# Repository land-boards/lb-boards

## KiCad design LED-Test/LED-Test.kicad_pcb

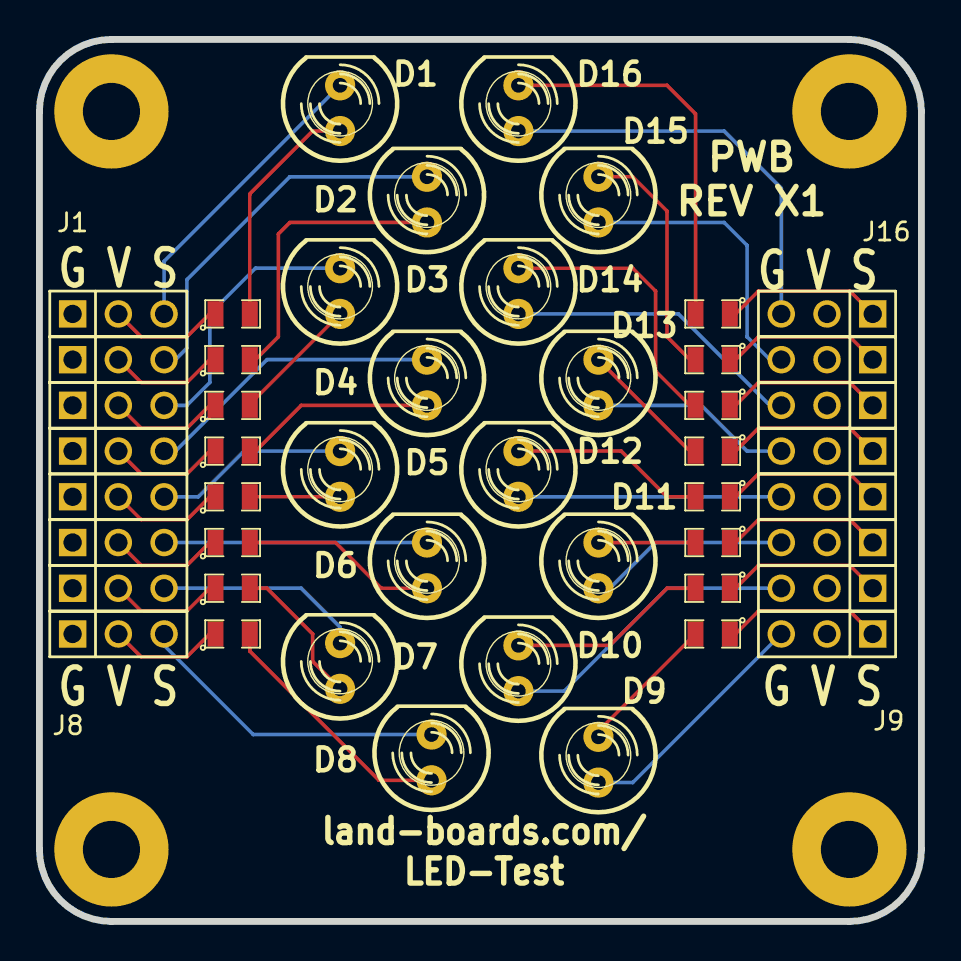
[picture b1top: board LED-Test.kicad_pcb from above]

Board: 2 copper layers, 49.0 x 49.0 mm, 52 parts (0 on the bottom side), 48 nets.

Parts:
D1, D2, D3, D4, D5, D6, D7, D8, D9, D10, D11, D12, D13, D14, D15, D16: LED; LED-5MM
J1, J2, J3, J4, J5, J6, J7, J8, J9, J10, J11, J12, J13, J14, J15, J16: CONN_3; PIN_ARRAY_3X1
MTG1, MTG2, MTG3, MTG4: CONN_1; MTG-4-40
R1, R2, R3, R4, R5, R6, R7, R8, R9, R10, R11, R12, R13, R14, R15, R16: 100; SM0805

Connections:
unnamed: J10.1, R10.1
unnamed: D10.1, J10.3
unnamed: D10.2, R10.2
unnamed: D11.2, R11.2
unnamed: J11.1, R11.1
unnamed: D11.1, J11.3
unnamed: D12.2, R12.2
unnamed: J12.1, R12.1
unnamed: J8.2, R8.1
unnamed: D8.2, J8.3
unnamed: D8.1, R8.2
unnamed: D12.1, J12.3
unnamed: D9.2, R9.2
unnamed: J9.1, R9.1
unnamed: D9.1, J9.3
unnamed: D14.2, R14.2
unnamed: D15.2, R15.2
unnamed: J15.1, R15.1
unnamed: D15.1, J15.3
unnamed: D16.2, R16.2
unnamed: J16.1, R16.1
unnamed: D16.1, J16.3
unnamed: D13.1, J13.3
unnamed: D13.2, R13.2
unnamed: J13.1, R13.1
unnamed: J14.1, R14.1
unnamed: D14.1, J14.3
unnamed: J3.2, R3.1
unnamed: D2.2, J2.3
unnamed: J2.2, R2.1
unnamed: D2.1, R2.2
unnamed: D3.1, R3.2
unnamed: D3.2, J3.3
unnamed: D4.1, R4.2
unnamed: D1.1, R1.2
unnamed: D1.2, J1.3
unnamed: J1.2, R1.1
unnamed: J6.2, R6.1
unnamed: D6.2, J6.3
unnamed: D6.1, R6.2
unnamed: D7.1, R7.2
unnamed: J7.2, R7.1
unnamed: D7.2, J7.3
unnamed: J4.2, R4.1
unnamed: D4.2, J4.3
unnamed: D5.1, R5.2
unnamed: J5.2, R5.1
unnamed: D5.2, J5.3

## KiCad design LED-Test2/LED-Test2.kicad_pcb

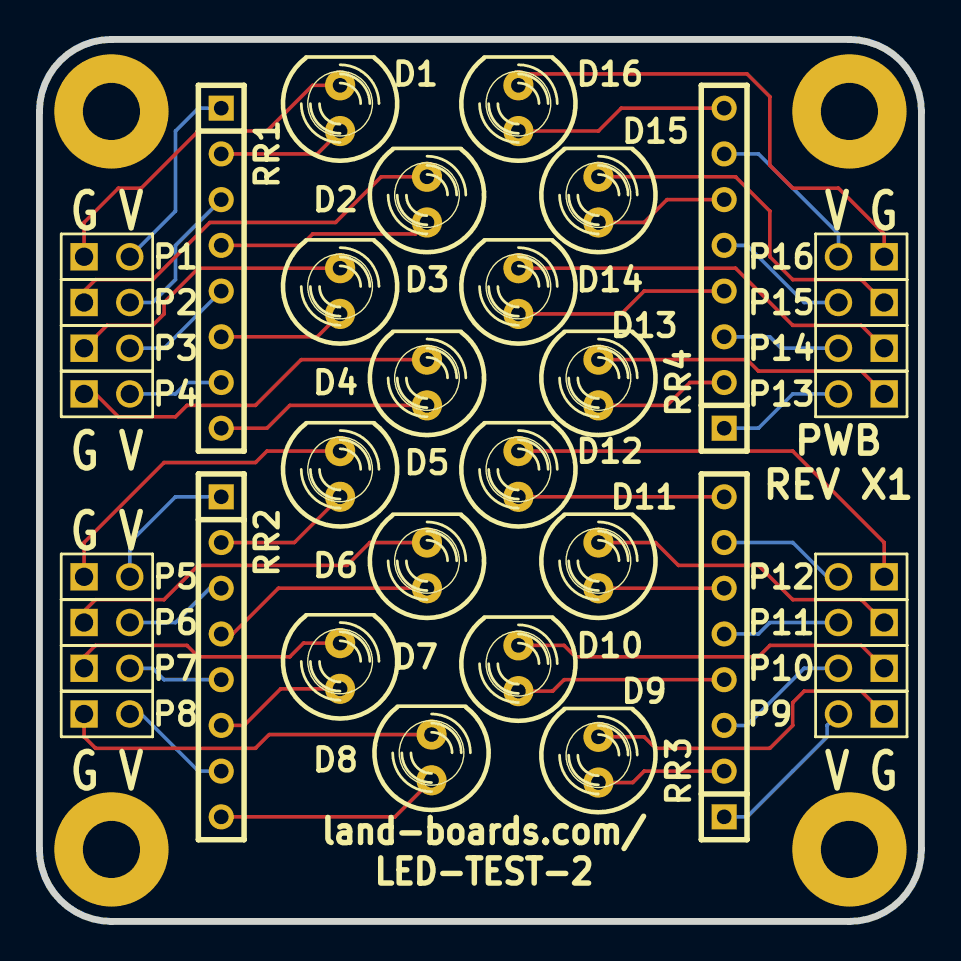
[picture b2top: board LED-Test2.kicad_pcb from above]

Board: 2 copper layers, 49.0 x 49.0 mm, 40 parts (0 on the bottom side), 48 nets.

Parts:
D1, D2, D3, D4, D5, D6, D7, D8, D9, D10, D11, D12, D13, D14, D15, D16: LED; LED-5MM
MTG1, MTG2, MTG3, MTG4: CONN_1; MTG-4-40
P1, P2, P3, P4, P5, P6, P7, P8, P9, P10, P11, P12, P13, P14, P15, P16: CONN_2; PIN_ARRAY_2X1
RR1, RR2, RR3, RR4: RR8; SIL-8

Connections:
unnamed: D5.1, RR2.2
unnamed: P6.2, RR2.3
unnamed: D6.1, RR2.4
unnamed: P7.2, RR2.5
unnamed: D7.1, RR2.6
unnamed: P8.2, RR2.7
unnamed: D8.1, RR2.8
unnamed: P10.2, RR3.3
unnamed: D10.1, RR3.4
unnamed: P11.2, RR3.5
unnamed: D11.1, RR3.6
unnamed: D2.1, RR1.4
unnamed: P3.2, RR1.5
unnamed: D3.1, RR1.6
unnamed: P4.2, RR1.7
unnamed: D4.1, RR1.8
unnamed: P9.2, RR3.1
unnamed: P5.2, RR2.1
unnamed: D14.1, RR4.4
unnamed: D15.1, RR4.6
unnamed: P13.2, RR4.1
unnamed: D13.1, RR4.2
unnamed: P14.2, RR4.3
unnamed: P15.2, RR4.5
unnamed: P16.2, RR4.7
unnamed: D16.1, RR4.8
unnamed: D9.1, RR3.2
unnamed: P12.2, RR3.7
unnamed: D12.1, RR3.8
unnamed: D6.2, P6.1
unnamed: D5.2, P5.1
unnamed: D7.2, P7.1
unnamed: D8.2, P8.1
unnamed: D9.2, P9.1
unnamed: D2.2, P2.1
unnamed: D1.1, RR1.2
unnamed: D1.2, P1.1
unnamed: P1.2, RR1.1
unnamed: D10.2, P10.1
unnamed: D3.2, P3.1
unnamed: D4.2, P4.1
unnamed: D14.2, P14.1
unnamed: D13.2, P13.1
unnamed: D15.2, P15.1
unnamed: P2.2, RR1.3
unnamed: D11.2, P11.1
unnamed: D12.2, P12.1
unnamed: D16.2, P16.1

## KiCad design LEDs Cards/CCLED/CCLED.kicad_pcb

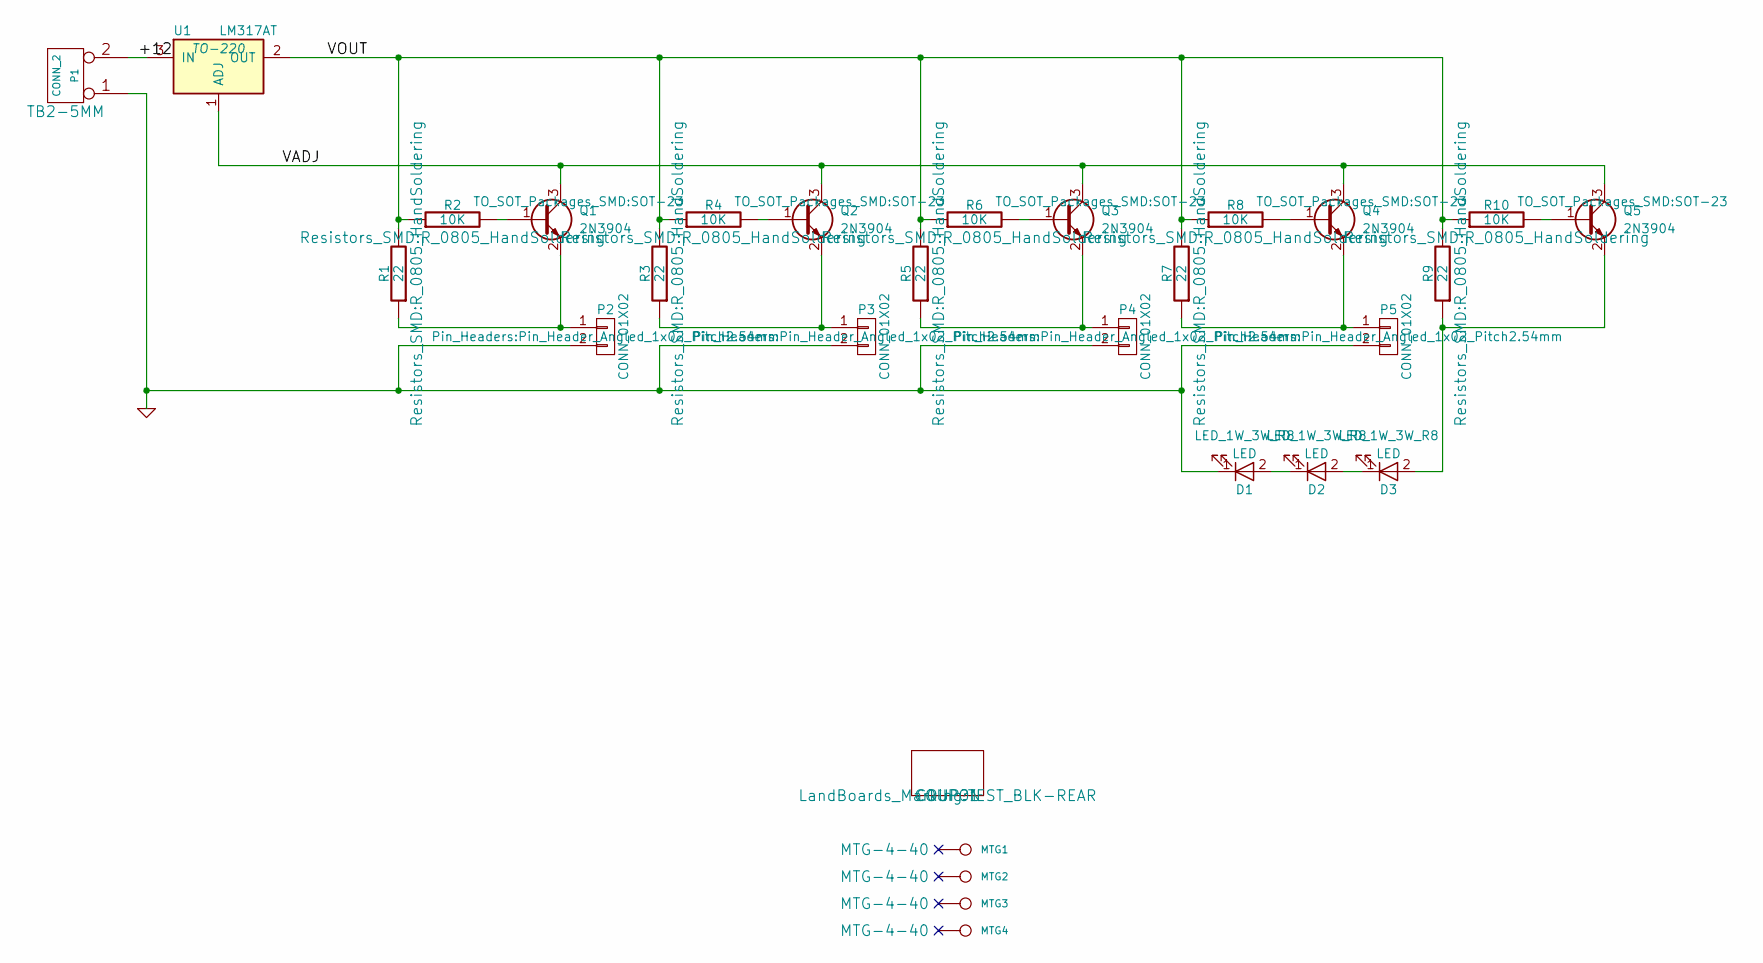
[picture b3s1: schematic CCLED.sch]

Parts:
COUP?1: COUPON; TEST_BLK-REAR
D1, D2, D3: LED; LED_1W_3W_R8
MTG1, MTG2, MTG3, MTG4: CONN_1; MTG-4-40
P1: CONN_2; TB2-5MM
P2, P3, P4, P5: CONN_01X02; Pin_Header_Angled_1x02_Pitch2.54mm
Q1, Q2, Q3, Q4, Q5: 2N3904; SOT-23
R1, R3, R5, R7, R9: 22; R_0805_HandSoldering
R2, R4, R6, R8, R10: 10K; R_0805_HandSoldering
U1: LM317AT; TO-220

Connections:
/+12: P1.2 (PM), U1.3 (IN)
/VADJ: Q1.3 (C), Q2.3 (C), Q3.3 (C), Q4.3 (C), Q5.3 (C), U1.1 (ADJ)
/VOUT: R1.2, R2.1, R3.2, R4.1, R5.2, R6.1, R7.2, R8.1, R9.2, R10.1, U1.2 (OUT)
GND: D1.1 (K), P1.1, P2.2, P3.2, P4.2, P5.2
unnamed: D1.2 (A), D2.1 (K)
unnamed: D2.2 (A), D3.1 (K)
unnamed: D3.2 (A), Q5.2 (E), R9.1
unnamed: P2.1, Q1.2 (E), R1.1
unnamed: P3.1, Q2.2 (E), R3.1
unnamed: P4.1, Q3.2 (E), R5.1
unnamed: P5.1, Q4.2 (E), R7.1
unnamed: Q1.1 (B), R2.2
unnamed: Q2.1 (B), R4.2
unnamed: Q3.1 (B), R6.2
unnamed: Q4.1 (B), R8.2
unnamed: Q5.1 (B), R10.2

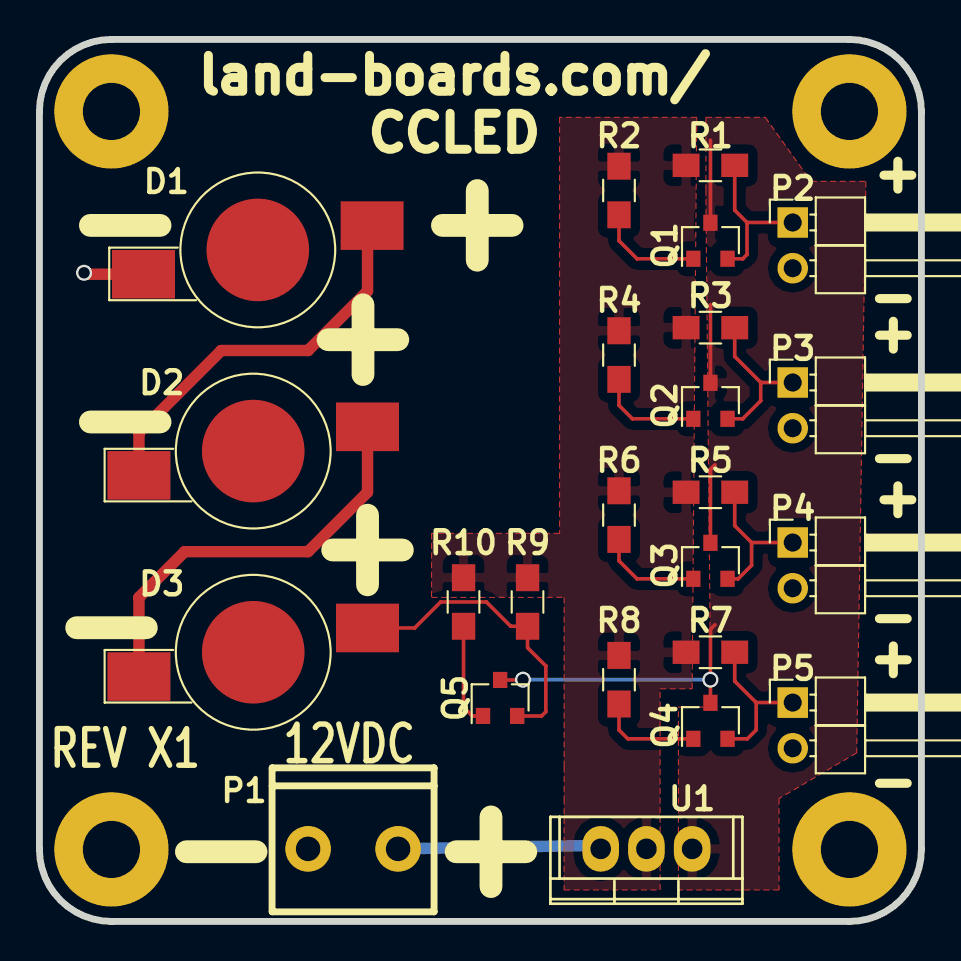
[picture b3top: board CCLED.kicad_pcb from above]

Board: 2 copper layers, 49.0 x 49.0 mm, 29 parts (0 on the bottom side), 16 nets.

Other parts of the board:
TEST: COUPON; TEST_BLK-REAR

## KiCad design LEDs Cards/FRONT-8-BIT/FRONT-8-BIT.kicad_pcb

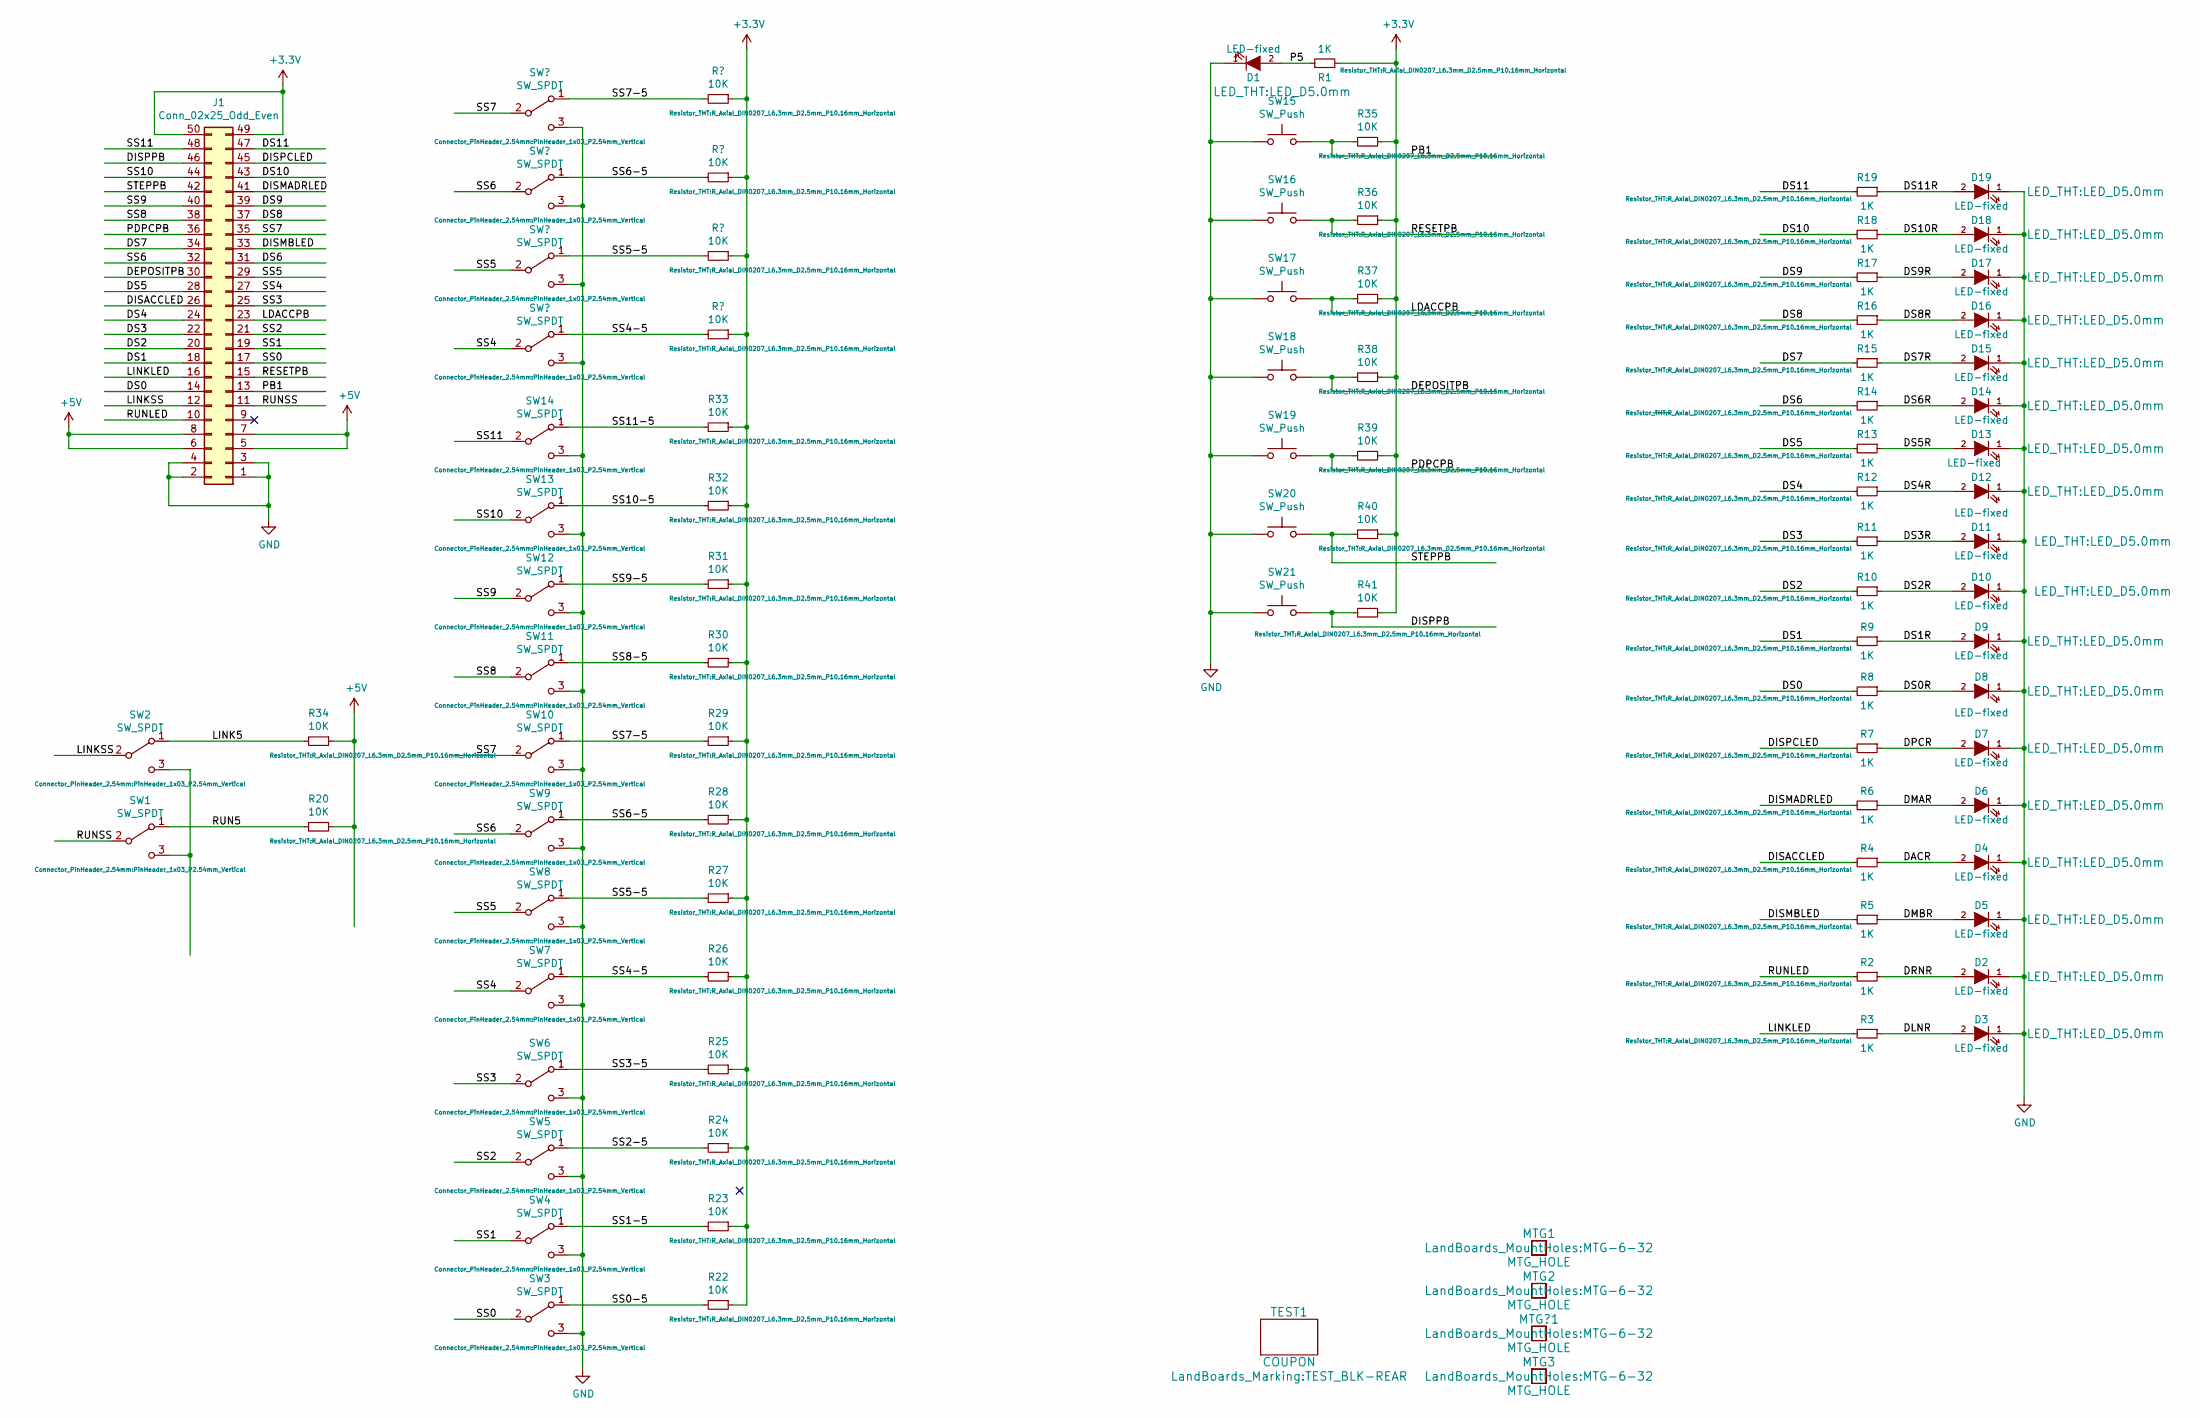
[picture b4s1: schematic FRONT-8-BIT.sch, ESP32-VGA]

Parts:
D1, D2, D3, D4, D5, D6, D7, D8, D9, D10, D11, D12, D13, D14, D15, D16, D17, D18, D19: LED-fixed; LED_D5.0mm
J1: Conn_02x25_Odd_Even; PinHeader_2x25_P2.54mm_Horizontal
MTG1, MTG2, MTG3: MTG_HOLE; MTG-6-32
MTG?1: MTG_HOLE; MTG-6-32
R1, R2, R3, R4, R5, R6, R7, R8, R9, R10, R11, R12, R13, R14, R15, R16, R17, R18, R19: 1K; R_Axial_DIN0207_L6.3mm_D2.5mm_P10.16mm_Horizontal
R20, R22, R23, R24, R25, R26, R27, R28, R29, R30, R31, R32, R33, R34, R35, R36, R37, R38, R39, R40, R41: 10K; R_Axial_DIN0207_L6.3mm_D2.5mm_P10.16mm_Horizontal
SW1, SW2, SW3, SW4, SW5, SW6, SW7, SW8, SW9, SW10, SW11, SW12, SW13, SW14: SW_SPDT; PinHeader_1x03_P2.54mm_Vertical
SW15, SW16, SW17, SW18, SW19, SW20, SW21: SW_Push; SW_PUSH_6mm_H8.5mm
TEST1: COUPON; TEST_BLK-REAR

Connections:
/DACR: D4.2 (A), R4.1
/DEPOSITPB: J1.30, R38.2, SW18.2
/DISACCLED: J1.26, R4.2
/DISMADRLED: J1.41, R6.2
/DISMBLED: J1.33, R5.2
/DISPCLED: J1.45, R7.2
/DISPPB: J1.46, R41.2, SW21.2
/DLNR: D3.2 (A), R3.1
/DMAR: D6.2 (A), R6.1
/DMBR: D5.2 (A), R5.1
/DPCR: D7.2 (A), R7.1
/DRNR: D2.2 (A), R2.1
/DS0: J1.14, R8.2
/DS0R: D8.2 (A), R8.1
/DS1: J1.18, R9.2
/DS1R: D9.2 (A), R9.1
/DS2: J1.20, R10.2
/DS2R: D10.2 (A), R10.1
/DS3: J1.22, R11.2
/DS3R: D11.2 (A), R11.1
/DS4: J1.24, R12.2
/DS4R: D12.2 (A), R12.1
/DS5: J1.28, R13.2
/DS5R: D13.2 (A), R13.1
/DS6: J1.31, R14.2
/DS6R: D14.2 (A), R14.1
/DS7: J1.34, R15.2
/DS7R: D15.2 (A), R15.1
/DS8: J1.37, R16.2
/DS8R: D16.2 (A), R16.1
/DS9: J1.39, R17.2
/DS9R: D17.2 (A), R17.1
/DS10: J1.43, R18.2
/DS10R: D18.2 (A), R18.1
/DS11: J1.47, R19.2
/DS11R: D19.2 (A), R19.1
/LDACCPB: J1.23, R37.2, SW17.2
/LINK5: R34.2, SW2.1 (A)
/LINKLED: J1.16, R3.2
/LINKSS: J1.12, SW2.2 (B)
/P5: D1.2 (A), R1.1
/PB1: J1.13, R35.2, SW15.2
/PDPCPB: J1.36, R39.2, SW19.2
/RESETPB: J1.15, R36.2, SW16.2
/RUN5: R20.2, SW1.1 (A)
/RUNLED: J1.10, R2.2
/RUNSS: J1.11, SW1.2 (B)
/SS0: J1.17, SW3.2 (B)
/SS0-5: R22.2, SW3.1 (A)
/SS1: J1.19, SW4.2 (B)
/SS1-5: R23.2, SW4.1 (A)
/SS2: J1.21, SW5.2 (B)
/SS2-5: R24.2, SW5.1 (A)
/SS3: J1.25, SW6.2 (B)
/SS3-5: R25.2, SW6.1 (A)
/SS4: J1.27, SW7.2 (B)
/SS4-5: R26.2, SW7.1 (A)
/SS5: J1.29, SW8.2 (B)
/SS5-5: R27.2, SW8.1 (A)
/SS6: J1.32, SW9.2 (B)
/SS6-5: R28.2, SW9.1 (A)
/SS7: J1.35, SW10.2 (B)
/SS7-5: R29.2, SW10.1 (A)
/SS8: J1.38, SW11.2 (B)
/SS8-5: R30.2, SW11.1 (A)
/SS9: J1.40, SW12.2 (B)
/SS9-5: R31.2, SW12.1 (A)
/SS10: J1.44, SW13.2 (B)
/SS10-5: R32.2, SW13.1 (A)
/SS11: J1.48, SW14.2 (B)
/SS11-5: R33.2, SW14.1 (A)
/STEPPB: J1.42, R40.2, SW20.2

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
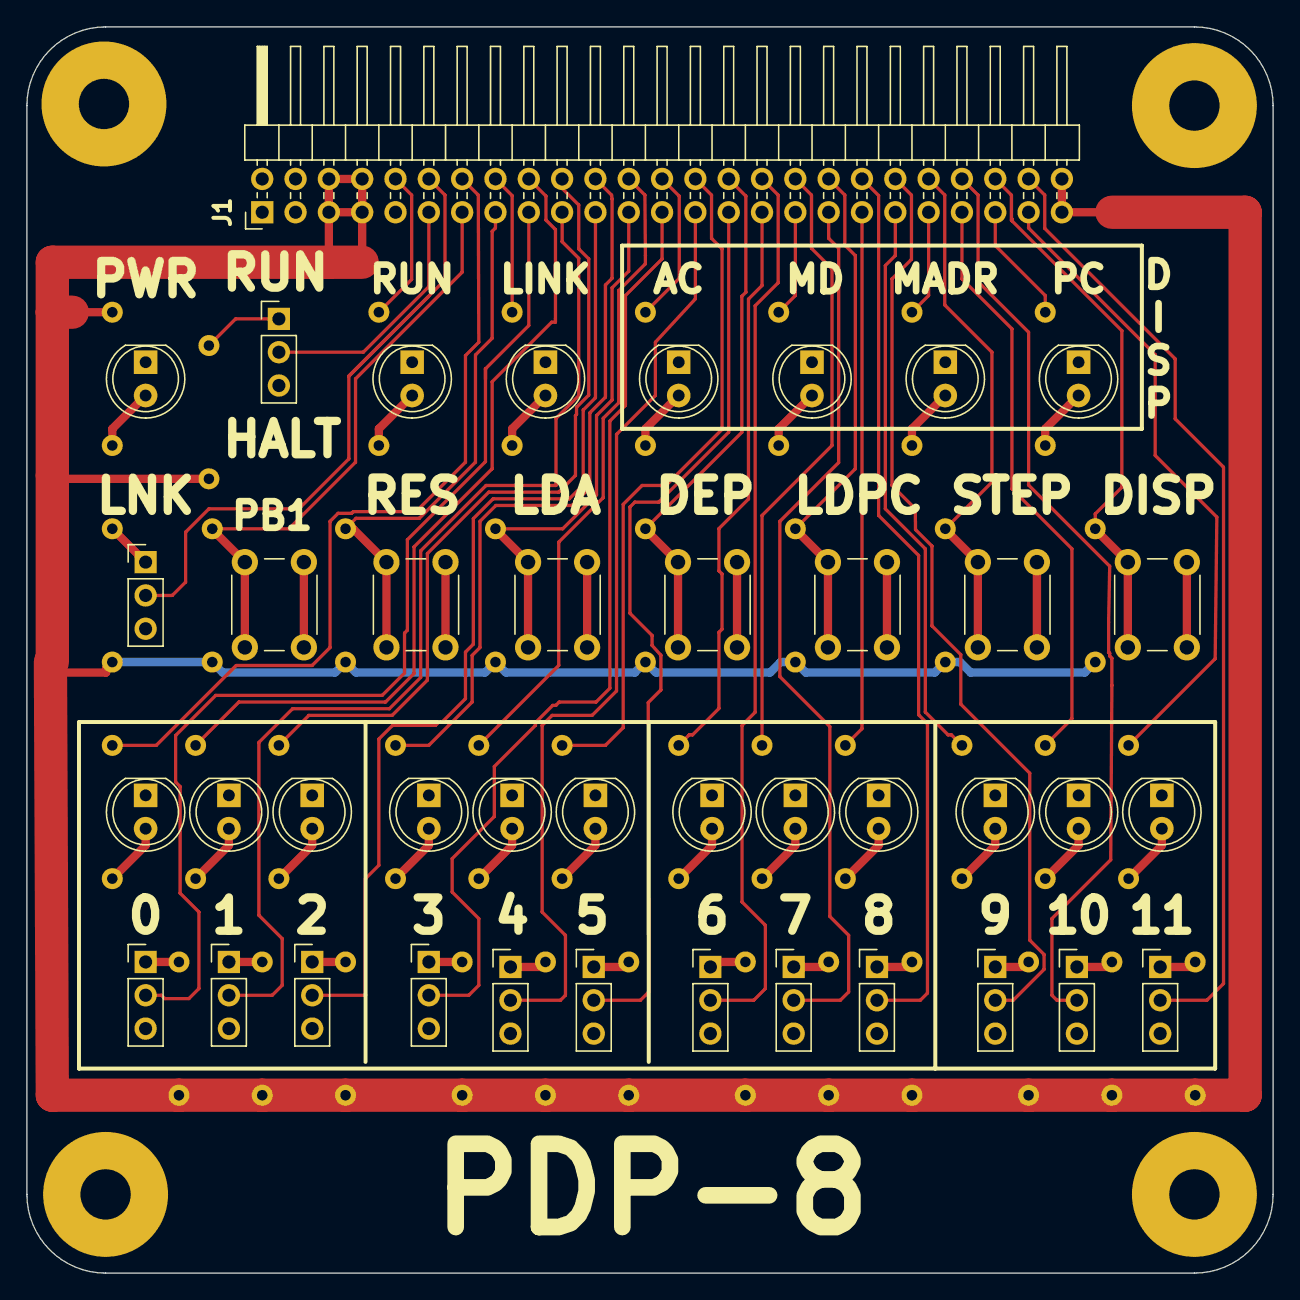
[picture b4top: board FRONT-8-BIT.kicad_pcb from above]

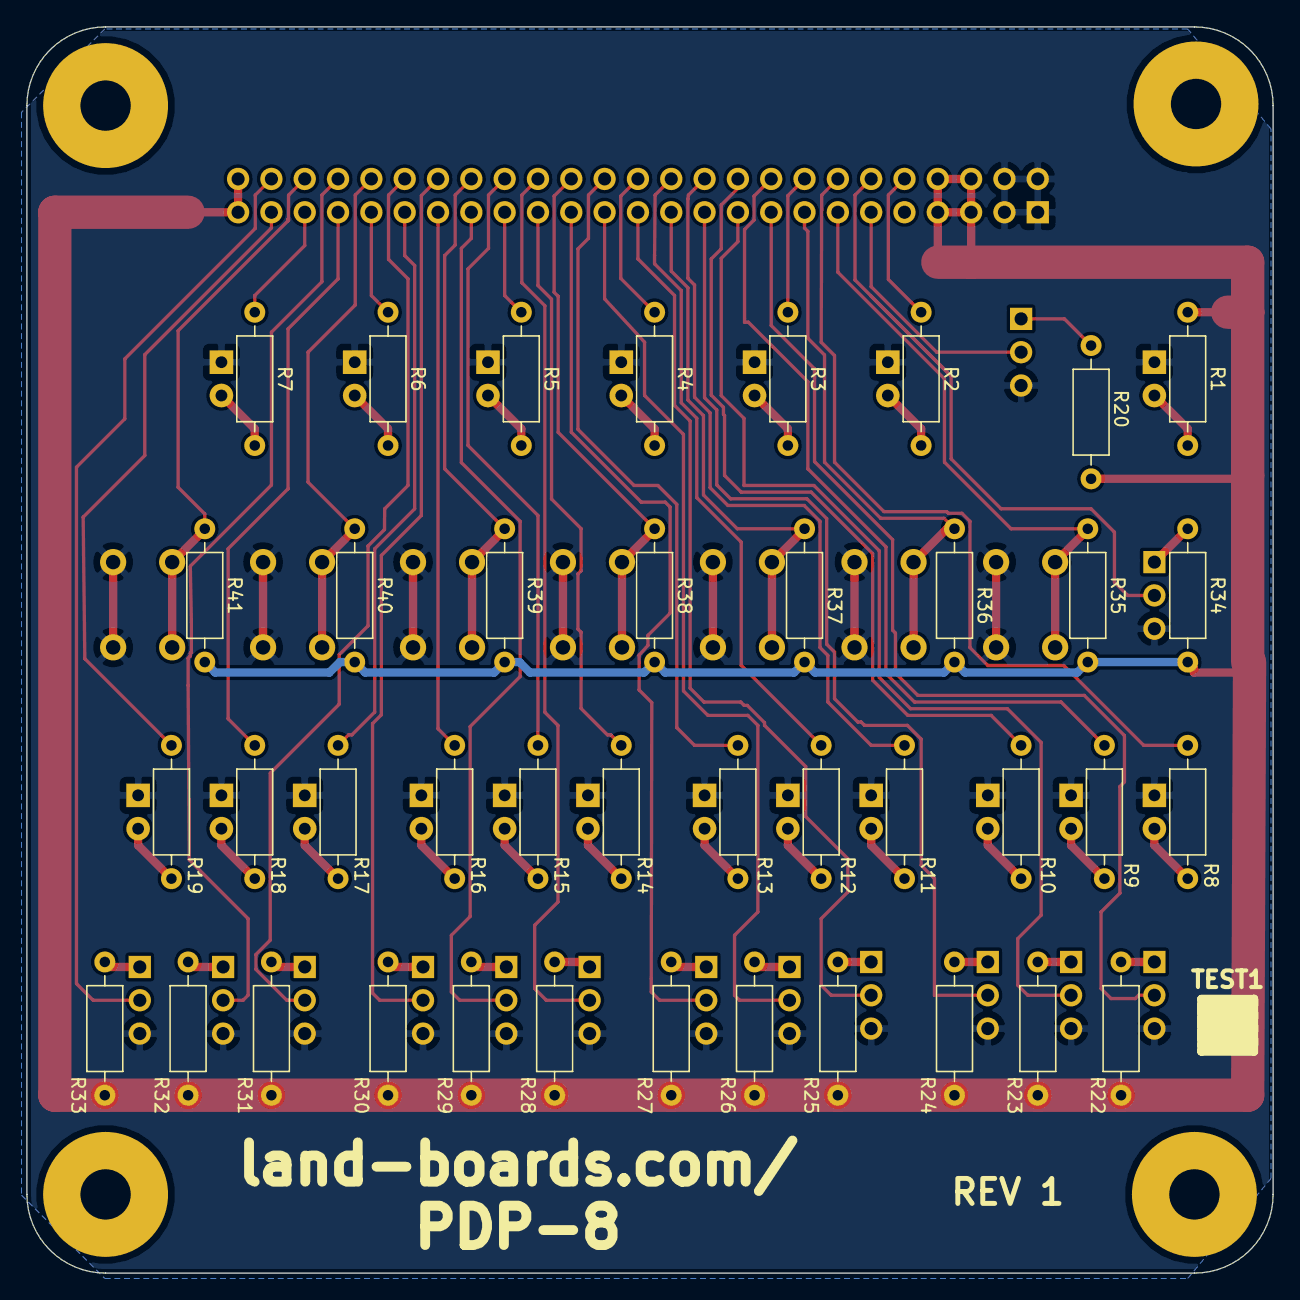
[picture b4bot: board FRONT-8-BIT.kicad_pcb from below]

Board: 2 copper layers, 95.0 x 95.0 mm, 86 parts (40 on the bottom side), 74 nets.

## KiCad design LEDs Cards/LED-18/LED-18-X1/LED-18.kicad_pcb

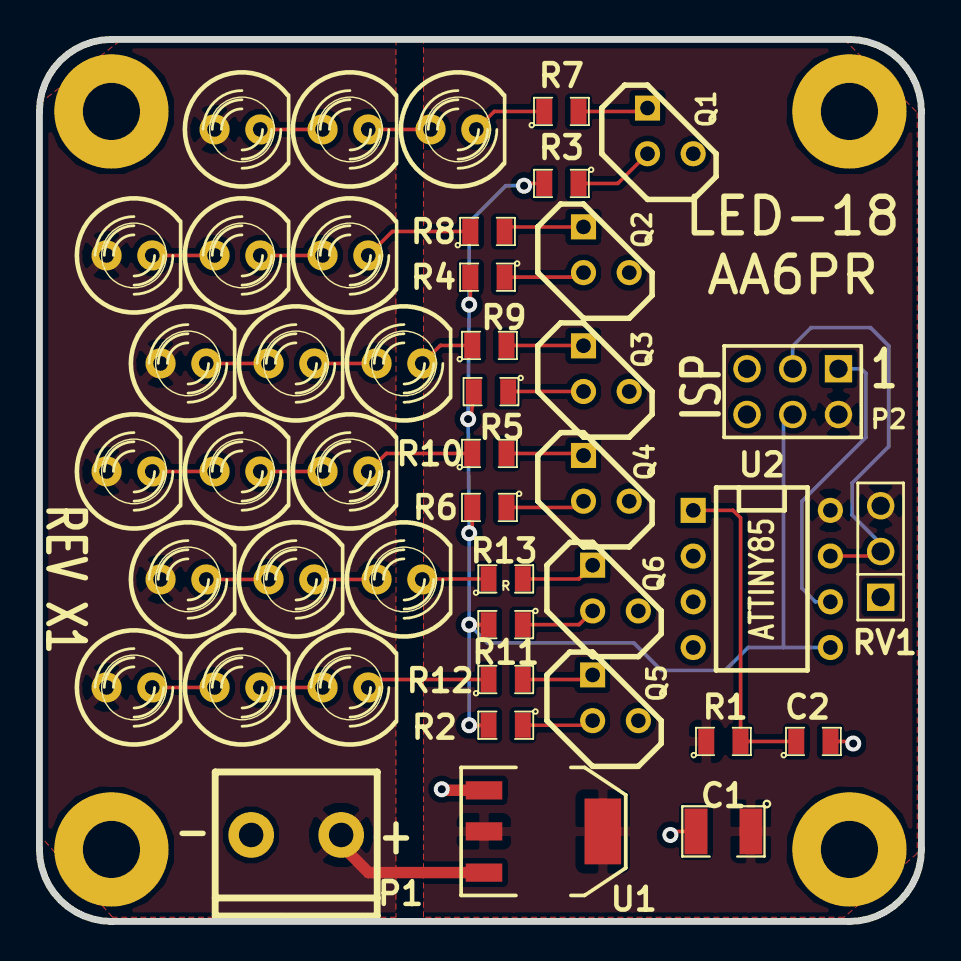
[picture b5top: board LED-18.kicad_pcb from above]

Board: 2 copper layers, 49.0 x 49.0 mm, 48 parts (0 on the bottom side), 37 nets.

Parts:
C1: 10uF; SM1210
C2: 0.1uF; SM0805
D1, D2, D3, D4, D5, D6, D7, D8, D9, D10, D11, D12, D13, D14, D15, D16, D17, D18: LED; LED-5MM
MTG1, MTG2, MTG3, MTG4: CONN_1; MTG-4-40
P1: CONN_2; TB2-5MM
P2: CONN_3X2; pin_array_3x2
Q1, Q2, Q3, Q4, Q5, Q6: NPN; TO92-123
R1: 10K; SM0805
R2, R3, R4, R5, R6, R11: 4.7K; SM0805
R7, R8, R9, R10, R12, R13: R; SM0805
RV1: 10K-POT; PIN_ARRAY_3X1
U1: AP1117; SOT223
U2: ATTINY85; DIP-8__300

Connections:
+5V: C1.1, P2.2, R1.1, RV1.3, U1.2, U1.4, U2.8
+12V: D1.1, D4.1, D7.1, D10.1, D13.1, D16.1, P1.1, U1.3
/MISO: P2.1, U2.6
/MOSI: P2.4, R2.2, R3.2, R4.2, R5.2, R6.2, R11.2, U2.5
/RES*: C2.1, R1.2, U2.1
/SCK: P2.3, RV1.2, U2.7
GND: C1.2, C2.2, P1.2, P2.6, Q1.1, Q2.1, Q3.1, Q4.1, Q5.1, Q6.1, RV1.1, U1.1, U2.4
unnamed: D16.2, D17.1
unnamed: Q6.3, R13.2
unnamed: D18.2, R13.1
unnamed: D17.2, D18.1
unnamed: D13.2, D14.1
unnamed: D14.2, D15.1
unnamed: D15.2, R12.1
unnamed: Q5.3, R12.2
unnamed: Q5.2, R2.1
unnamed: Q6.2, R11.1
unnamed: Q1.2, R3.1
unnamed: Q2.2, R4.1
unnamed: Q3.2, R5.1
unnamed: Q1.3, R7.2
unnamed: Q4.2, R6.1
unnamed: D8.2, D9.1
unnamed: Q3.3, R9.2
unnamed: D9.2, R9.1
unnamed: D7.2, D8.1
unnamed: D10.2, D11.1
unnamed: D11.2, D12.1
unnamed: D12.2, R10.1
unnamed: Q4.3, R10.2
unnamed: Q2.3, R8.2
unnamed: D6.2, R8.1
unnamed: D5.2, D6.1
unnamed: D4.2, D5.1
unnamed: D1.2, D2.1
unnamed: D2.2, D3.1
unnamed: D3.2, R7.1

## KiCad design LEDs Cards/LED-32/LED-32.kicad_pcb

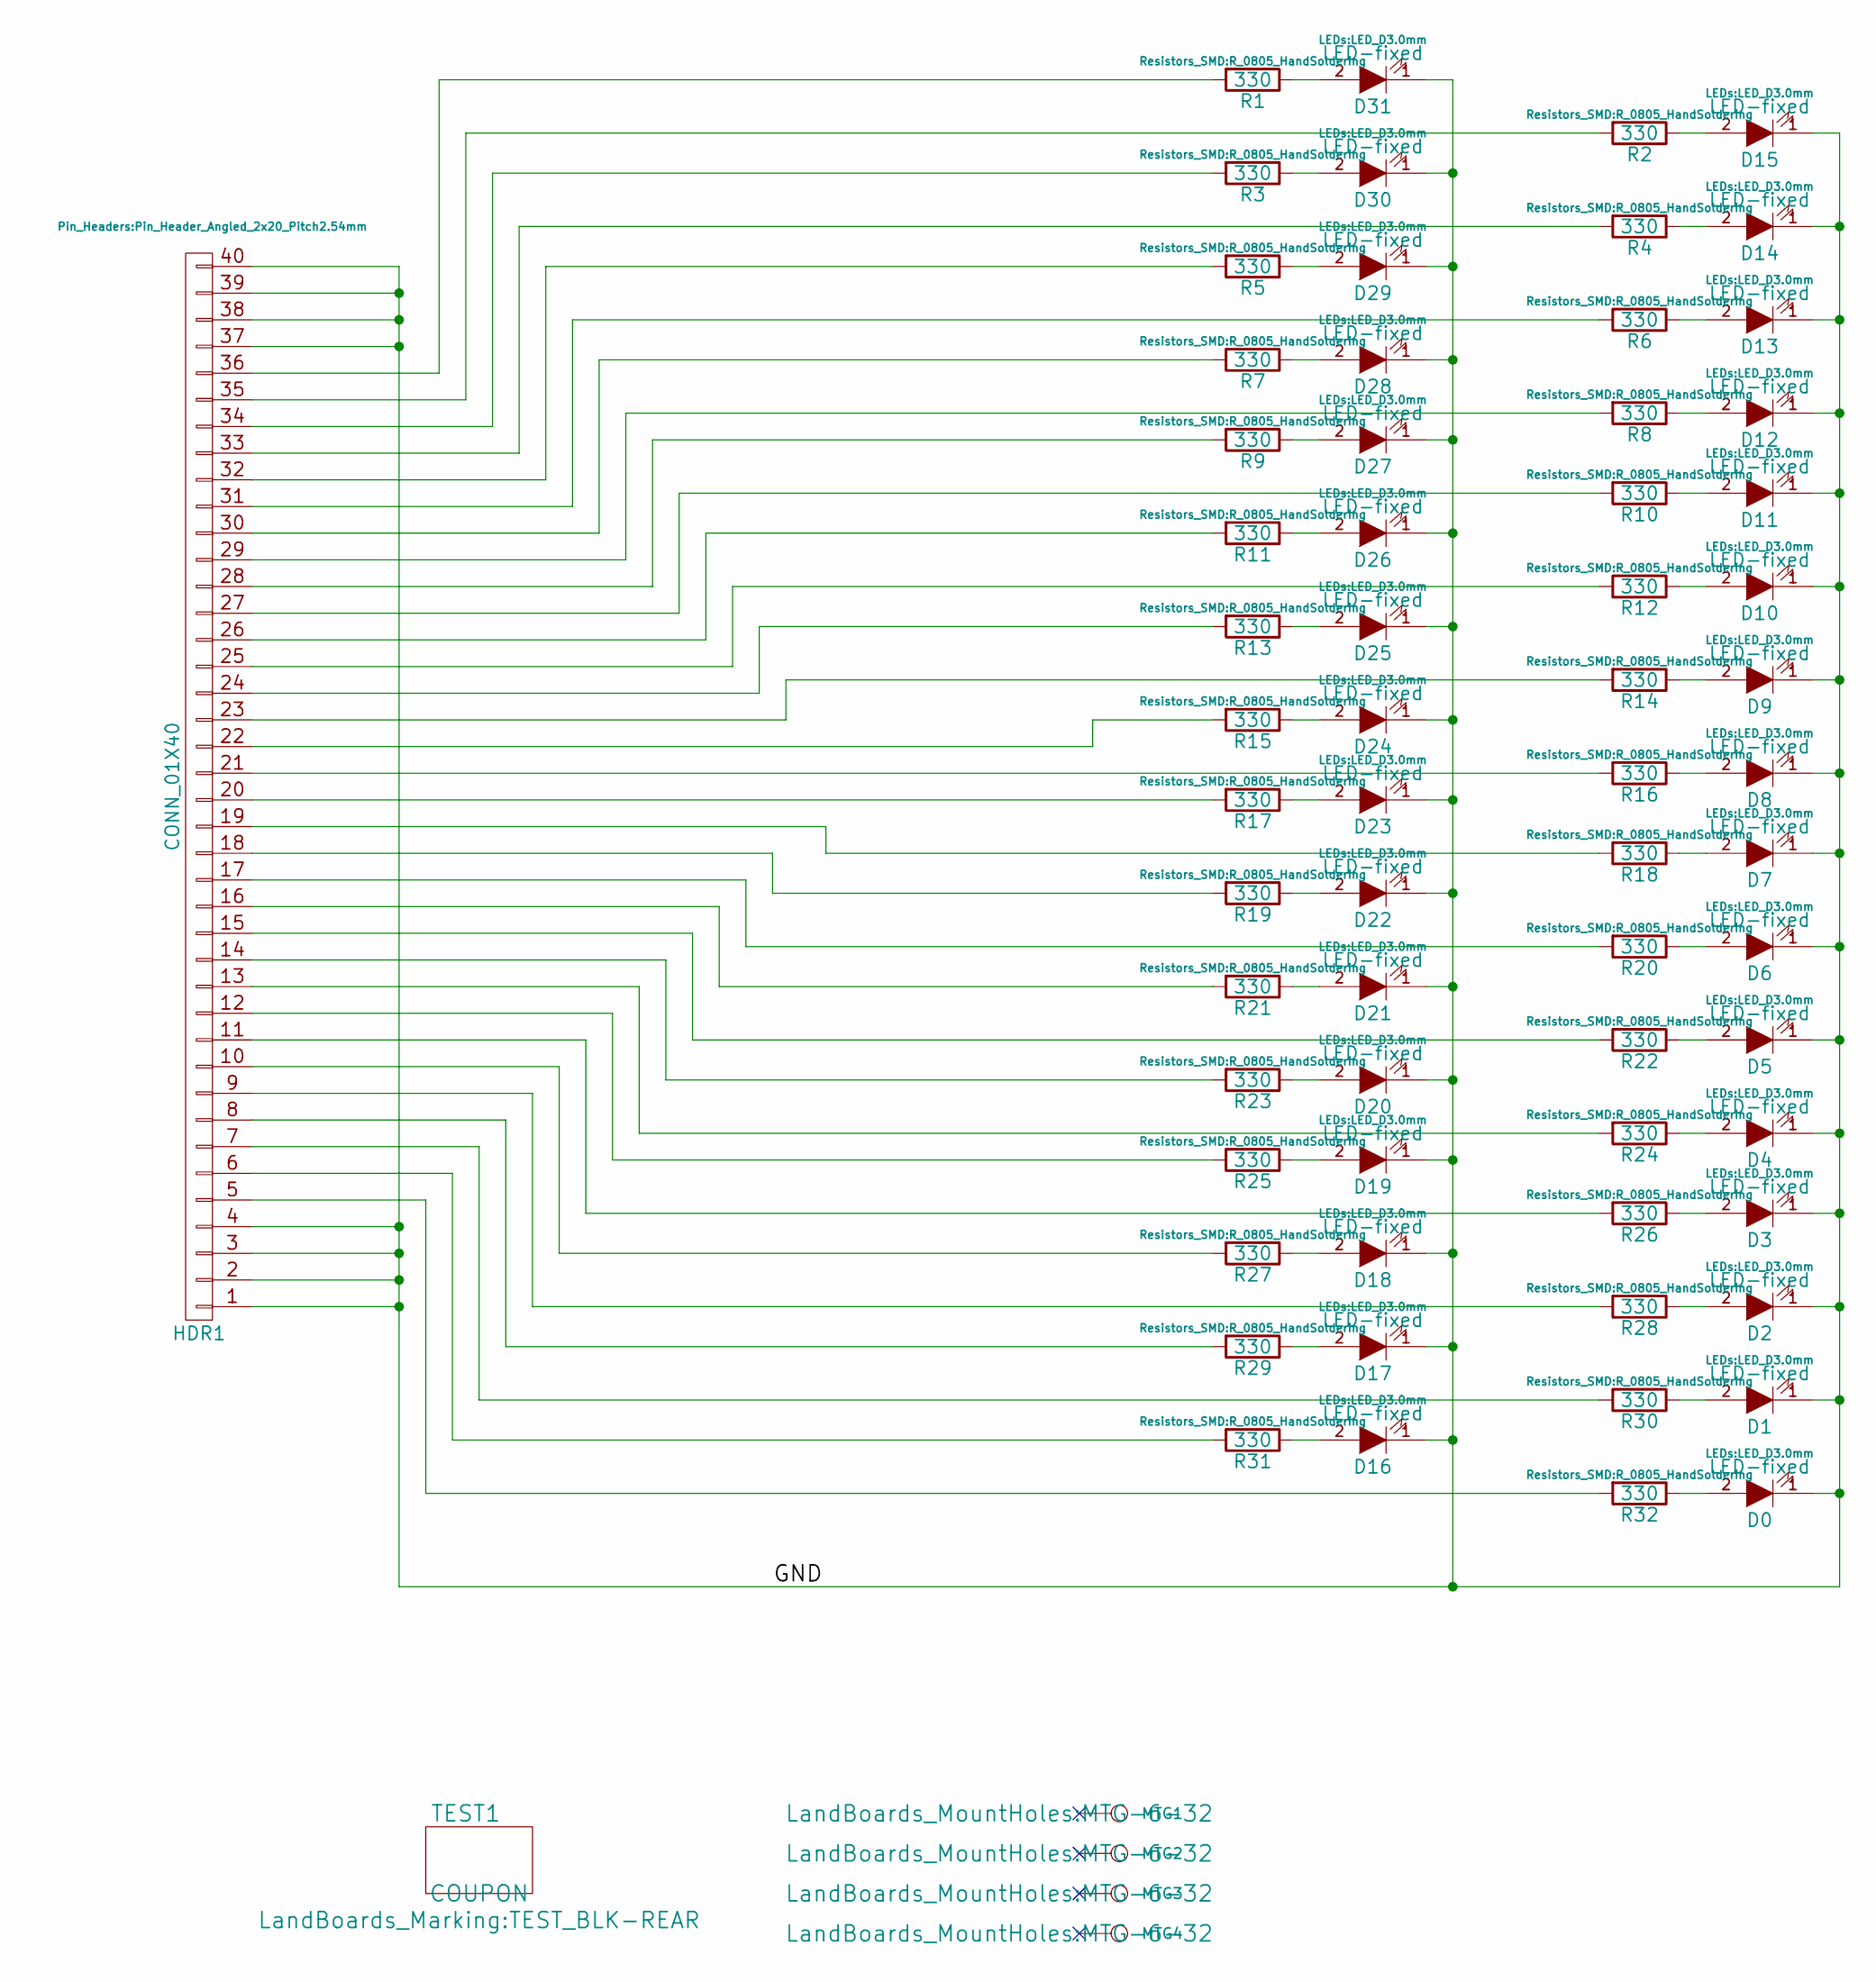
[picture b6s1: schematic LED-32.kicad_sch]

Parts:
D0, D1, D2, D3, D4, D5, D6, D7, D8, D9, D10, D11, D12, D13, D14, D15, D16, D17, D18, D19, D20, D21, D22, D23, D24, D25, D26, D27, D28, D29, D30, D31: LED-fixed; LED_D3.0mm
HDR1: CONN_01X40; Pin_Header_Angled_2x20_Pitch2.54mm
MTG1, MTG2, MTG3, MTG4: CONN_1; MTG-6-32
R1, R2, R3, R4, R5, R6, R7, R8, R9, R10, R11, R12, R13, R14, R15, R16, R17, R18, R19, R20, R21, R22, R23, R24, R25, R26, R27, R28, R29, R30, R31, R32: 330; R_0805_HandSoldering
TEST1: COUPON; TEST_BLK-REAR

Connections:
/GND: D0.1 (K), D1.1 (K), D2.1 (K), D3.1 (K), D4.1 (K), D5.1 (K), D6.1 (K), D7.1 (K), D8.1 (K), D9.1 (K), D10.1 (K), D11.1 (K), D12.1 (K), D13.1 (K), D14.1 (K), D15.1 (K), D16.1 (K), D17.1 (K), D18.1 (K), D19.1 (K), D20.1 (K), D21.1 (K), D22.1 (K), D23.1 (K), D24.1 (K), D25.1 (K), D26.1 (K), D27.1 (K), D28.1 (K), D29.1 (K), D30.1 (K), D31.1 (K), HDR1.1, HDR1.2, HDR1.3, HDR1.4, HDR1.37, HDR1.38, HDR1.39, HDR1.40
unnamed: D0.2 (A), R32.1
unnamed: D1.2 (A), R30.1
unnamed: D2.2 (A), R28.1
unnamed: D3.2 (A), R26.1
unnamed: D4.2 (A), R24.1
unnamed: D5.2 (A), R22.1
unnamed: D6.2 (A), R20.1
unnamed: D7.2 (A), R18.1
unnamed: D8.2 (A), R16.1
unnamed: D9.2 (A), R14.1
unnamed: D10.2 (A), R12.1
unnamed: D11.2 (A), R10.1
unnamed: D12.2 (A), R8.1
unnamed: D13.2 (A), R6.1
unnamed: D14.2 (A), R4.1
unnamed: D15.2 (A), R2.1
unnamed: D16.2 (A), R31.1
unnamed: D17.2 (A), R29.1
unnamed: D18.2 (A), R27.1
unnamed: D19.2 (A), R25.1
unnamed: D20.2 (A), R23.1
unnamed: D21.2 (A), R21.1
unnamed: D22.2 (A), R19.1
unnamed: D23.2 (A), R17.1
unnamed: D24.2 (A), R15.1
unnamed: D25.2 (A), R13.1
unnamed: D26.2 (A), R11.1
unnamed: D27.2 (A), R9.1
unnamed: D28.2 (A), R7.1
unnamed: D29.2 (A), R5.1
unnamed: D30.2 (A), R3.1
unnamed: D31.2 (A), R1.1
unnamed: HDR1.5, R32.2
unnamed: HDR1.6, R31.2
unnamed: HDR1.7, R30.2
unnamed: HDR1.8, R29.2
unnamed: HDR1.9, R28.2
unnamed: HDR1.10, R27.2
unnamed: HDR1.11, R26.2
unnamed: HDR1.12, R25.2
unnamed: HDR1.13, R24.2
unnamed: HDR1.14, R23.2
unnamed: HDR1.15, R22.2
unnamed: HDR1.16, R21.2
unnamed: HDR1.17, R20.2
unnamed: HDR1.18, R19.2
unnamed: HDR1.19, R18.2
unnamed: HDR1.20, R17.2
unnamed: HDR1.21, R16.2
unnamed: HDR1.22, R15.2
unnamed: HDR1.23, R14.2
unnamed: HDR1.24, R13.2
unnamed: HDR1.25, R12.2
unnamed: HDR1.26, R11.2
unnamed: HDR1.27, R10.2
unnamed: HDR1.28, R9.2
unnamed: HDR1.29, R8.2
unnamed: HDR1.30, R7.2
unnamed: HDR1.31, R6.2
unnamed: HDR1.32, R5.2
unnamed: HDR1.33, R4.2
unnamed: HDR1.34, R3.2
unnamed: HDR1.35, R2.2
unnamed: HDR1.36, R1.2
